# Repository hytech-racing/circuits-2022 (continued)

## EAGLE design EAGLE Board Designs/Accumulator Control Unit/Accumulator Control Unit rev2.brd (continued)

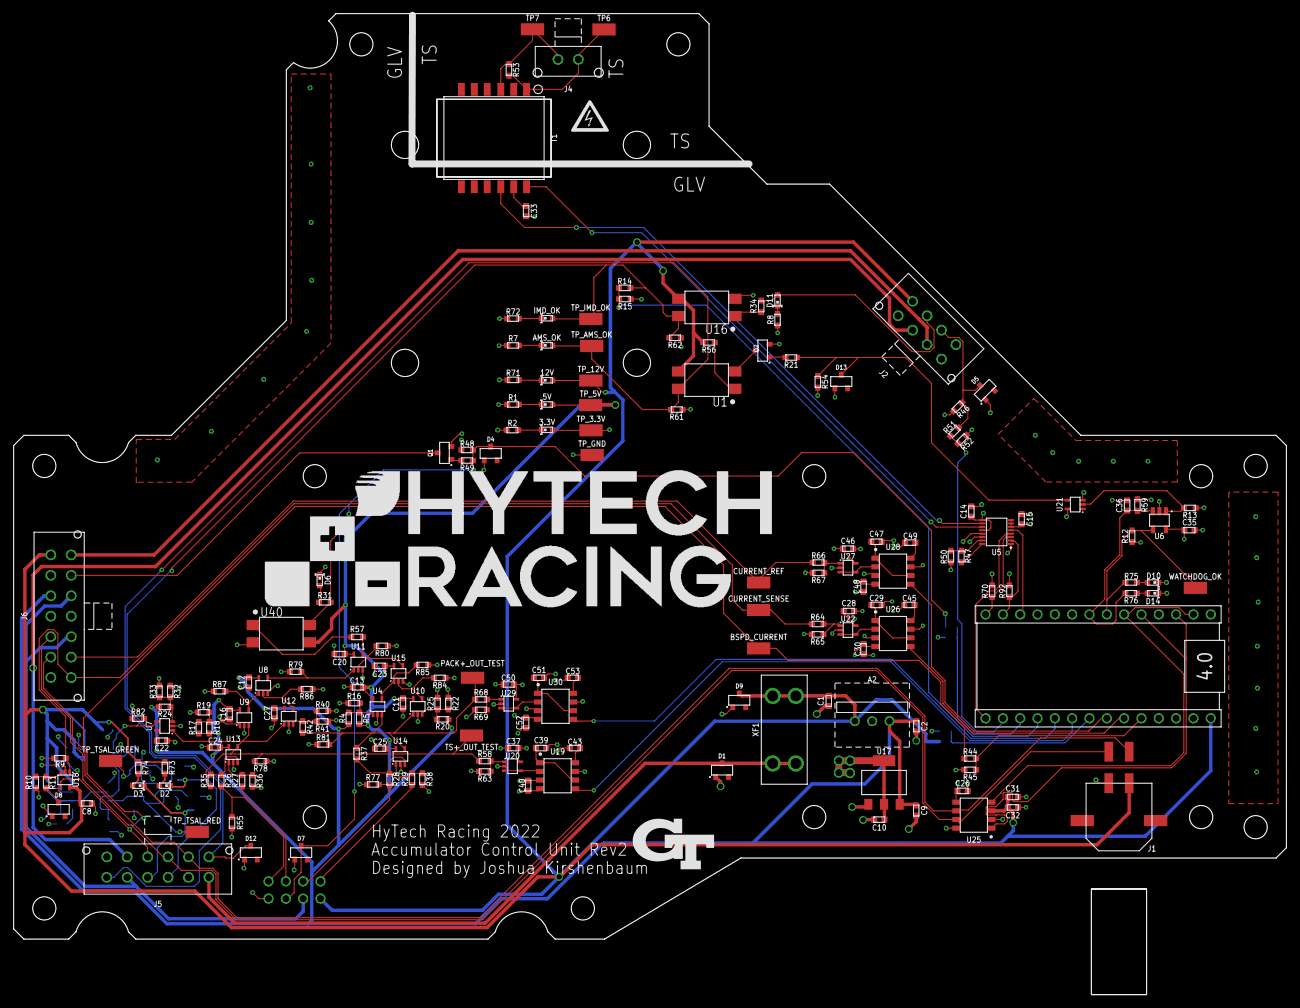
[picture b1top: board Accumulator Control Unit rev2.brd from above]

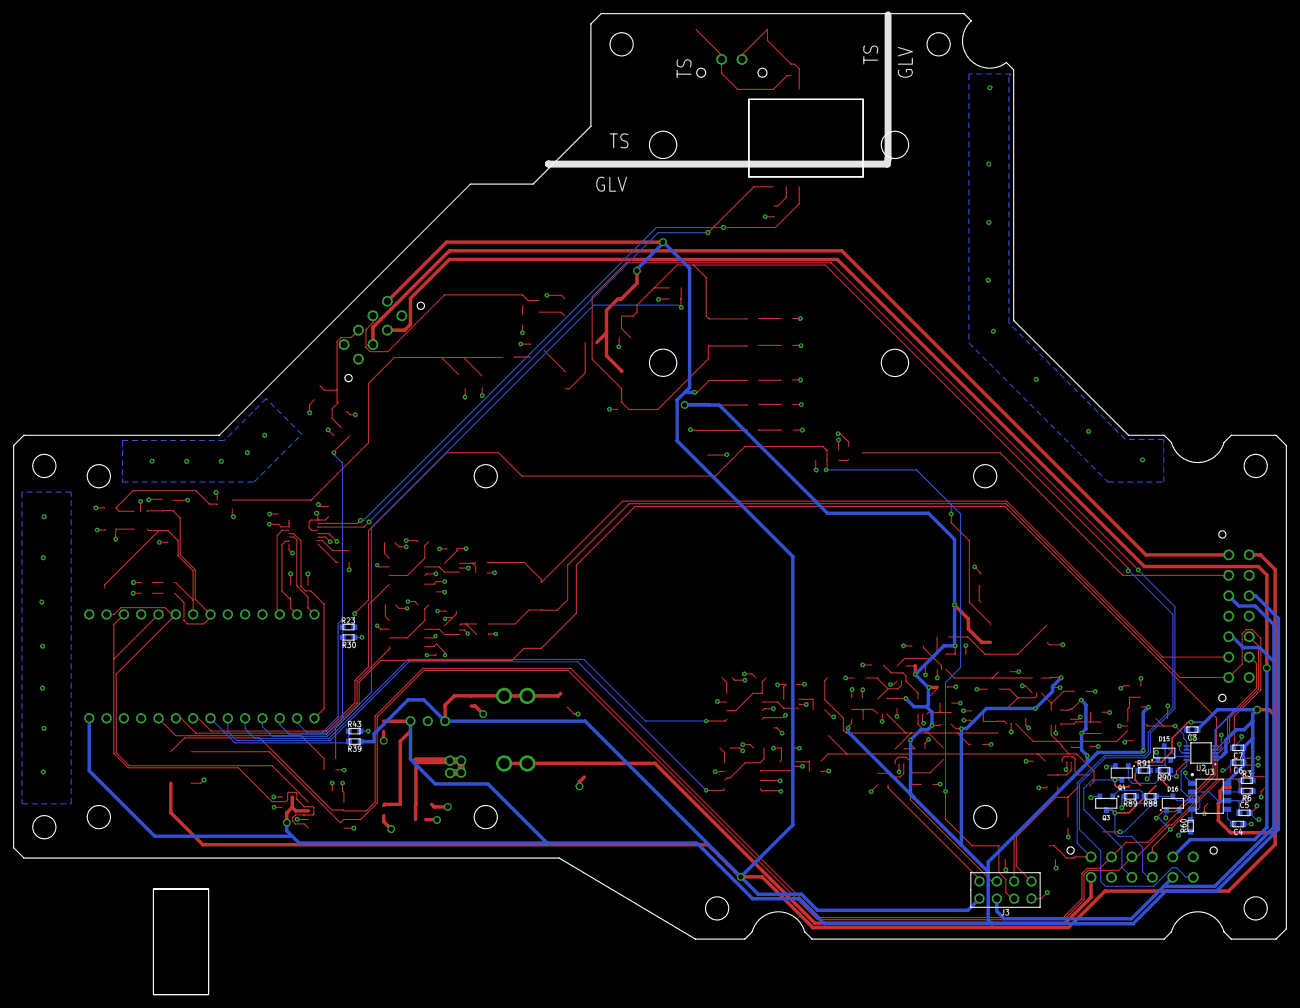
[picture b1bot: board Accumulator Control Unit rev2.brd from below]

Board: 4 copper layers, 186.7 x 143.9 mm, 236 parts (23 on the bottom side), 112 nets.

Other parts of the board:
U$1, U$5: GLV
U$3, U$9, U$10: TS
U$4: HV_0.50"
U$6, U$7, U$8, U$11, U$12, U$13, U$14, U$17, U$18, U$19, U$20, U$21, U$22: MOUNTING_M3
U$15: LOGO_HYTECH_EXTRA_LARGE
U$16: LOGO_GT_0.50"

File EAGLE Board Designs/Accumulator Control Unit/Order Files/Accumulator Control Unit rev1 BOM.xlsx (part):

Qty | Value | Device | Package | Parts | Description | CAPACITANCE | COLOR | CURRENT | DKPN | MANUFACTURER | MOPN | MPN | POWER | RESET_VOLTAGE | RESISTANCE | TOLERANCE | VOLTAGE | VOLTAGE_CONTINUOUS | VOLTAGE_MAX | Column1
1 | ADG1423 | ADG1423 | MSOP-10 | U2 | ADG1423 Form-A/Form-C Analog Switch |  |  |  | ADG1423BRMZ-REEL7CT-ND | Analog Devices Inc. | 584-ADG1423BRMZ | ADG1423BRMZ
1 | ADM823 | ADM823 | SC-70-5 | U6 | ADM823 Watchdog |  |  |  | 505-ADM823TYKSZ-R7CT-ND | Analog Devices Inc. | 584-ADM823TYKSZ-R7 | ADM823TYKSZ-R7 |  | 3.08
24 | CAPACITOR_0603_10V_0.1UF | CAPACITOR_0603_10V_0.1UF | 0603-CAP | C11, C12, C13, C14, C15, C16, C20, C22, C23, C24, C25, C26, C27, C29, C30, C31,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 | Capacitor, Non-Polarized | 0.1µF |  |  | 720-1688-1-ND | Vishay Vitramon | 77-VJ0603Y104JXQPBC | VJ0603Y104JXQPW1BC |  |  |  | 0.05 | 10V
2 | CAPACITOR_0603_10V_10NF | CAPACITOR_0603_10V_10NF | 0603-CAP | C4, C33 | Capacitor, Non-Polarized | 10nF |  |  | 311-4054-1-ND | Yageo | 603-CC603KRX7R6BB103 | CC0603KRX7R6BB103 |  |  |  | 0.1 | 10V
1 | CAPACITOR_0603_10V_15PF | CAPACITOR_0603_10V_15PF | 0603-CAP | C34 | Capacitor, Non-Polarized | 15pF |  |  | 720-VJ0603A150FXQPW1BCCT-ND | Vishay Vitramon | 77-VJ0603A150FXQPBC | VJ0603A150FXQPW1BC |  |  |  | 0.01 | 10V
2 | CAPACITOR_0603_10V_1UF | CAPACITOR_0603_10V_1UF | 0603-CAP | C9, C32 | Capacitor, Non-Polarized | 1µF |  |  | 311-1796-1-ND | Yageo | 603-CC603KRX7R6BB105 | CC0603KRX7R6BB105 |  |  |  | 0.1 | 10V
2 | CAPACITOR_0603_10V_4.7UF | CAPACITOR_0603_10V_4.7UF | 0603-CAP | C5, C10 | Capacitor, Non-Polarized | 4.7µF |  |  | 1276-1044-1-ND | Samsung Electro-Mechanics | 187-CL10A475KP8NNNC | CL10A475KP8NNNC |  |  |  | 0.1 | 10V
4 | CAPACITOR_0603_10V_680PF | CAPACITOR_0603_10V_680PF | 0603-CAP | C43, C45, C49, C53 | Capacitor, Non-Polarized | 680pF |  |  | 732-7757-1-ND | Würth Elektronik | 710-885012006013 | 885012006013 |  |  |  | 0.05 | 10V
6 | CAPACITOR_0603_25V_0.1UF | CAPACITOR_0603_25V_0.1UF | 0603-CAP | C7, C8, C28, C37, C46, C50 | Capacitor, Non-Polarized | 0.1µF |  |  | 1276-1006-1-ND | Samsung Electro-Mechanics | 187-CL10B104KA8NNNC | CL10B104KA8NNNC |  |  |  | 0.1 | 25V
2 | CAPACITOR_0603_25V_10UF | CAPACITOR_0603_25V_10UF | 0603-CAP | C1, C2 | Capacitor, Non-Polarized | 10µF |  |  | 490-7202-1-ND | Murata Electronics | 81-GRM188R61E106MA3D | GRM188R61E106MA73D |  |  |  | 0.2 | 25V
2 | CAPACITOR_0603_25V_1UF | CAPACITOR_0603_25V_1UF | 0603-CAP | C3, C6 | Capacitor, Non-Polarized | 1µF |  |  | 1276-1184-1-ND | Samsung Electro-Mechanics | 187-CL10B105KA8NNNC | CL10B105KA8NNNC |  |  |  | 0.1 | 25V
1 | CONNECTOR-12_MF_T_V_ | CONNECTOR-12_MF_T_V_ | MOLEX_MICROFIT_PTH_VERTICAL_12_DUAL | J5 | 12 pin connector |  |  |  |  | MOLEX |  | 430451214
1 | CONNECTOR-14_MF_T_V_ | CONNECTOR-14_MF_T_V_ | MOLEX_MICROFIT_PTH_VERTICAL_14_DUAL | J6 | 14 pin connector |  |  |  |  | MOLEX |  | 430451414
1 | CONNECTOR-2_MF_T_V_ | CONNECTOR-2_MF_T_V_ | MOLEX_MICROFIT_PTH_VERTICAL_02_SINGLE | J4 | 2 Pin Connector |  |  |  |  | MOLEX |  | 436500217
2 | CONNECTOR-8_MF_T_V_ | CONNECTOR-8_MF_T_V_ | MOLEX_MICROFIT_PTH_VERTICAL_08_DUAL | J2, J3 | 8 Pin Connector |  |  |  |  | MOLEX |  | 430450814
1 | CONNECTOR-CAN_MF_T_V_ | CONNECTOR-CAN_MF_T_V_ | MOLEX_MICROFIT_PTH_VERTICAL_04_DUAL | J1 | HyTech CAN Connector |  |  |  |  | Molex |  | 430450414
1 | FUSE_MINI-BLADE_1A | FUSE_MINI-BLADE_1A | MINI-BLADE_FUSE_HOLDER | F1 | Fuse |  |  | 1A
1 | LED_0603_BLUE | LED_0603_BLUE | 0603-LED | 5V | LED |  | Blue |  | 754-1789-1-ND | Kingbright | 604-APT1608VBC/D | APT1608VBC/D
4 | LED_0603_GREEN | LED_0603_GREEN | 0603-LED | 3.3V, AMS_OK, D2, D10 | LED |  | Green |  | 754-1790-1-ND | Kingbright | 604-APT1608ZGCK | APT1608ZGCK
1 | LED_0603_ORANGE | LED_0603_ORANGE | 0603-LED | IMD_OK | LED |  | Orange |  | 754-1120-1-ND | Kingbright | 604-APT1608SECK | APT1608SECK
4 | LED_0603_RED | LED_0603_RED | 0603-LED | 12V, D3, D6, D14 | LED |  | Red |  | 754-1786-1-ND | Kingbright | 604-APT1608SECKJ3PRV | APT1608SECK/J3-PRV
1 | LED_0603_YELLOW | LED_0603_YELLOW | 0603-LED | D11 | LED |  | Yellow |  | 754-1788-1-ND | Kingbright | 604-APT1608SYCK/J3-PRV | APT1608SYCK/J3-PRV
1 | LM555 | LM555 | SOIC-08(NARROW,0.15)" | U3 | **555 Precision Timer |  |  |  | LM555CMX/NOPBCT-ND | Texas Instruments | 926-LM555CMX/NOPB | LM555CMX/NOPB
3 | LOGICGATE_AND_DCK3 | LOGICGATE_AND_DCK3 | SC-70-5 | U8, U11, U15 | AND Gate |  |  |  | 296-SN74LVC1G08DCK3TR-ND | Texas Instruments | 595-SN74LVC1G08DCK3 | SN74LVC1G08DCK3
1 | LTC6820 | LTC6820 | MSOP-16 | U5 | LTC6820 isoSPI Isolated Communications Interface |  |  |  |  | Analog Devices |  | LTC6820IMS#PBF
4 | MAX7404 | MAX7404 | SOIC-08(NARROW,0.15)" | U19, U26, U28, U30 | 8th-Order Maxim Filter |  |  |  | MAX7404CSA+-ND | Maxim Integrated | 700-MAX7404CSA | MAX7404CSA+
12 | OPAMP_1_CHANNEL_OPA991 | OPAMP_1_CHANNEL_OPA991 | SC-70-5 | U4, U7, U9, U10, U12, U13, U14, U18, U20, U22, U27, U29 | Op-Amp 1 Channel |  |  |  | 296-OPA991IDCKRCT-ND | Texas Instruments | 595-OPA991IDCKR | OPA991IDCKR
3 | RELAY_SOLIDSTATE_NO | RELAY_SOLIDSTATE_NO | DIP-4 | U$2, U1, U16 | AQY214EH Normally Open Solid State Relay |  |  |  |  |  |  | AQY214EHA
1 | RESISTOR_0603_1.4K | RESISTOR_0603_1.4K | 0603-RES | R11 | Resistor |  |  |  | 311-2465-1-ND | Yageo | 603-RT0603DRE071K4L | RT0603DRE071K4L | 0.1W |  | 1.4K | 5.0000000000000001E-3 |  | 75V | 75V
2 | RESISTOR_0603_10 | RESISTOR_0603_10 | 0603-RES | R21, R49 | Resistor |  |  |  | 311-10.0HRCT-ND | Yageo | 603-RC0603FR-0710RL | RC0603FR-0710RL | 0.1W |  | 10 | 0.01 |  | 1V | 75V
2 | RESISTOR_0603_10.2K | RESISTOR_0603_10.2K | 0603-RES | R16, R19 | Resistor |  |  |  | P10.2KDBCT-ND | Panasonic Electronic Components | 667-ERA-3AEB1022V | ERA-3AEB1022V | 0.1W |  | 10.2k | 1E-3 |  | 31.94V | 75V
4 | RESISTOR_0603_10.5K | RESISTOR_0603_10.5K | 0603-RES | R35, R36, R37, R38 | Resistor |  |  |  | P10.5KDBCT-ND | Panasonic Electronic Components | 677-ERA-3AEB1052V | ERA-3AEB1052V | 0.1W |  | 10.5k | 1E-3 |  | 32.40V | 75V
1 | RESISTOR_0603_100K | RESISTOR_0603_100K | 0603-RES | R13 | Resistor |  |  |  | YAG2294CT-ND | Yageo | 603-RC0603JR-10100KL | RC0603JR-10100KL | 0.1W |  | 100k | 0.05 |  | 75V | 75V
23 | RESISTOR_0603_10K | RESISTOR_0603_10K | 0603-RES | R9, R12, R23, R48, R54, R55, R58, R60, R61, R62, R64, R66, R68, R77, R78, R79, 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 | Resistor |  |  |  | 311-10.0KHRCT-ND | Yageo | 603-RC0603FR-0710KL | RC0603FR-0710KL | 0.1W |  | 10k | 0.01 |  | 31.62V | 75V
1 | RESISTOR_0603_11.3K | RESISTOR_0603_11.3K | 0603-RES | R42 | Resistor |  |  |  | P11.3KDBCT-ND | Panasonic Electronic Components | 667-ERA-3AEB1132V | ERA-3AEB1132V | 0.1W |  | 11.3k | 1E-3 |  | 33.62V | 75V
7 | RESISTOR_0603_11.5K | RESISTOR_0603_11.5K | 0603-RES | R20, R25, R26, R27, R28, R29, R33 | Resistor |  |  |  | P11.5KDBCT-ND | Panasonic Electronic Components | 667-ERA-3AEB1152V | ERA-3AEB1152V | 0.1W |  | 11.5k | 1E-3 |  | 33.91V | 75V
9 | RESISTOR_0603_12K | RESISTOR_0603_12K | 0603-RES | R15, R30, R43, R45, R52, R63, R65, R67, R69 | Resistor |  |  |  | 311-12.0KHRCT-ND | Yageo | 603-RC0603FR-0712KL | RC0603FR-0712KL | 0.1W |  | 12k | 0.01 |  | 34.64V | 75V
12 | RESISTOR_0603_1K | RESISTOR_0603_1K | 0603-RES | R1, R2, R3, R7, R8, R10, R31, R47, R50, R59, R70, R71 | Resistor |  |  |  | 311-1.00KHRCT-ND | Yageo | 603-RC0603FR-071KL | RC0603FR-071KL | 0.1W |  | 1k | 0.01 |  | 10.00V | 75V
1 | RESISTOR_0603_2.2K | RESISTOR_0603_2.2K | 0603-RES | R46 | Resistor |  |  |  | 13-RC0603DR-072K2LCT-ND | Yageo | 603-RC0603DR-072K2L | RC0603DR-072K2L | 0.1W |  | 2.2k | 5.0000000000000001E-3 |  | 75V | 75V
1 | RESISTOR_0603_215K | RESISTOR_0603_215K | 0603-RES | R41 | Resistor |  |  |  | P215KDBCT-ND | Panasonic Electronic Components | 667-ERA-3AEB2153V | ERA-3AEB2153V | 0.1W |  | 215k | 1E-3 |  | 75V | 75V
5 | RESISTOR_0603_2K | RESISTOR_0603_2K | 0603-RES | R34, R56, R72, R73, R74 | Resistor |  |  |  | P2.0KBDCT-ND | Panasonic Electronic Components | 667-ERA-3ARB202V | ERA-3ARB202V | 0.1W |  | 2k | 1E-3 |  | 14.14V | 75V
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
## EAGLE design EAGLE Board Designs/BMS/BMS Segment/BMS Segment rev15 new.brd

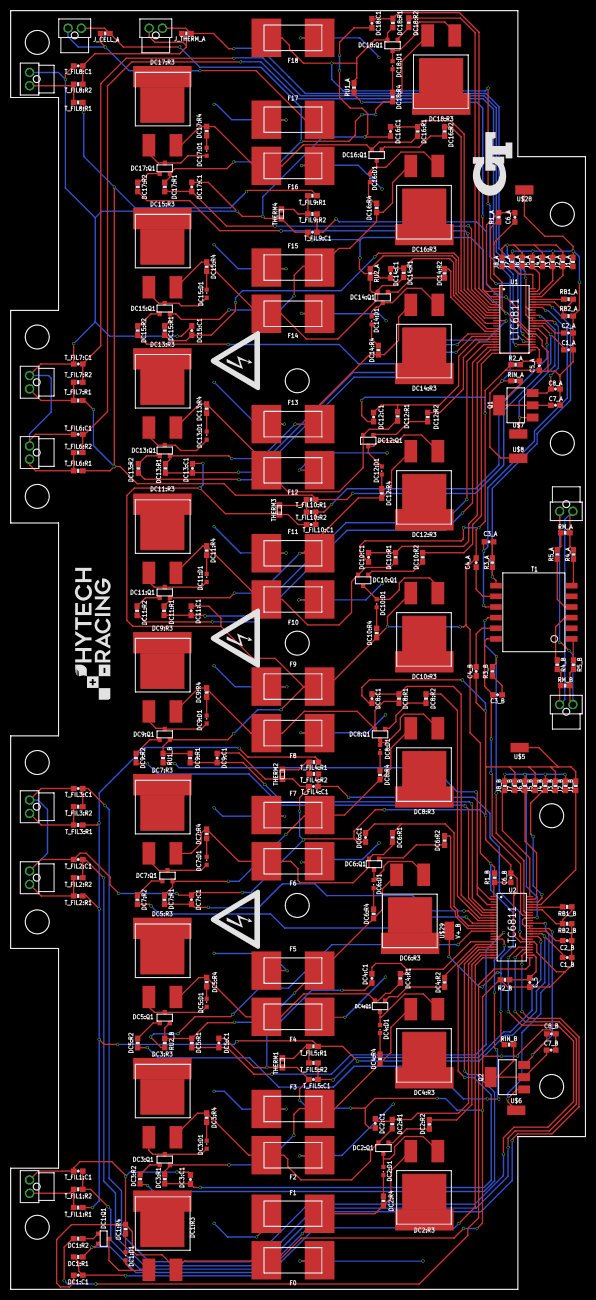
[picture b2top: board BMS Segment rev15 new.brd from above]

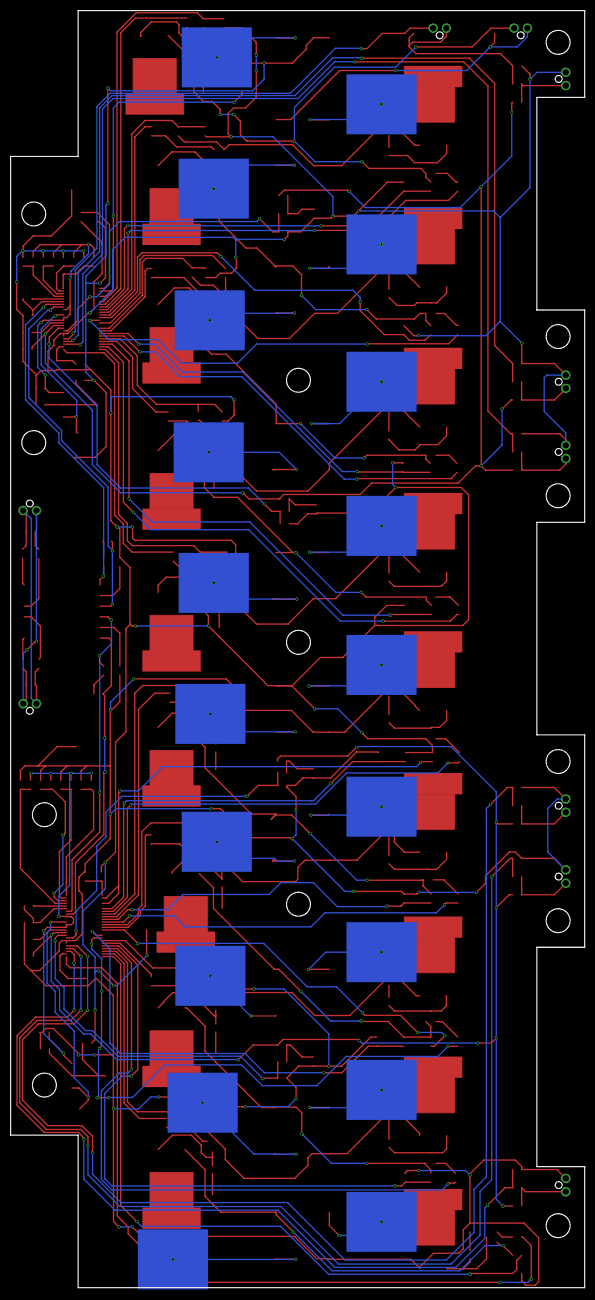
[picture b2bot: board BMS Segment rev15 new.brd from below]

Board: 2 copper layers, 108.0 x 240.3 mm, 294 parts (19 on the bottom side), 194 nets.

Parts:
AMS_CELL_TEST: AMS_CELL_TEST; NANO-FIT_VERTICAL-2
AMS_THERM_TEST: AMS_THERM_TEST; NANO-FIT_VERTICAL-2
C1_A, C1_B, C2_A, C2_B, C8_A, C8_B: 1uF; 0603-CAP
C3_A, C3_B: 15pF; 0603-CAP
C4_A, C4_B, C5_A: 10nF; 0603-CAP
C6_A, C6_B, C7_A, C7_B: 100nF; 0603-CAP
CELL0, CELL1, CELL2, CELL3, CELL4, CELL5, CELL6, CELL7, CELL8, CELL9, CELL10, CELL11, CELL12, CELL13, CELL14, CELL15, CELL16, CELL17, CELL18: BATTERY_SPRING_KEYSTONE5222; KEYSTONE5222
C_5: 10nF; 0603-CAP
DC1:C1, DC2:C1, DC3:C1, DC4:C1, DC5:C1, DC6:C1, DC7:C1, DC8:C1, DC9:C1, DC10:C1, DC11:C1, DC12:C1, DC13:C1, DC14:C1, DC15:C1, DC16:C1, DC17:C1, DC18:C1: 10nF; 0603-CAP
DC1:D1, DC2:D1, DC3:D1, DC4:D1, DC5:D1, DC6:D1, DC7:D1, DC8:D1, DC9:D1, DC10:D1, DC11:D1, DC12:D1, DC13:D1, DC14:D1, DC15:D1, DC16:D1, DC17:D1, DC18:D1: RED; LED-603
DC1:Q1, DC2:Q1, DC3:Q1, DC4:Q1, DC5:Q1, DC6:Q1, DC7:Q1, DC8:Q1, DC9:Q1, DC10:Q1, DC11:Q1, DC12:Q1, DC13:Q1, DC14:Q1, DC15:Q1, DC16:Q1, DC17:Q1, DC18:Q1: P-CHANNEL_MOSFET_DMP3099L-7; SOT23
DC1:R1, DC2:R1, DC3:R1, DC4:R1, DC5:R1, DC6:R1, DC7:R1, DC8:R1, DC9:R1, DC10:R1, DC11:R1, DC12:R1, DC13:R1, DC14:R1, DC15:R1, DC16:R1, DC17:R1, DC18:R1: 100R; 0603-RES@1
DC1:R2, DC2:R2, DC3:R2, DC4:R2, DC5:R2, DC6:R2, DC7:R2, DC8:R2, DC9:R2, DC10:R2, DC11:R2, DC12:R2, DC13:R2, DC14:R2, DC15:R2, DC16:R2, DC17:R2, DC18:R2: 3K3; 0603-RES@1
DC1:R3, DC2:R3, DC3:R3, DC4:R3, DC5:R3, DC6:R3, DC7:R3, DC8:R3, DC9:R3, DC10:R3, DC11:R3, DC12:R3, DC13:R3, DC14:R3, DC15:R3, DC16:R3, DC17:R3, DC18:R3: RESISTOR_PWR263_; PWR263
DC1:R4, DC2:R4, DC3:R4, DC4:R4, DC5:R4, DC6:R4, DC7:R4, DC8:R4, DC9:R4, DC10:R4, DC11:R4, DC12:R4, DC13:R4, DC14:R4, DC15:R4, DC16:R4, DC17:R4, DC18:R4: 806R; 0603-RES@1
F0, F1, F2, F3, F4, F5, F6, F7, F8, F9, F10, F11, F12, F13, F14, F15, F16, F17, F18: 0001.2704.11; 0885
ISOSPI_A: ISOSPI; NANO-FIT_VERTICAL-2
ISOSPI_B: ISOSPI; NANO-FIT_VERTICAL-2
J1_A, J1_B, J2_A, J2_B, J3_A, J3_B, J4_A, J4_B, J5_A, J5_B, J6_A, J6_B, J7_A, J7_B, J8_A, J8_B: 0R; 0603-RES@1
J_CELL_A: 0R; 0603-RES@1
J_THERM_A: 0R; 0603-RES@1
Q1, Q2: NSV1C201MZ4; SOT223
R1_A, R1_B, R2_A, R2_B: 100R; 0603-RES@1
R3_A, R3_B: 402R; 0603-RES@1
R4_A, R4_B, R5_A, R5_B: 22R; 0603-RES@1
RB1_A, RB1_B: 1K2; 0603-RES@1
RB2_A, RB2_B: 806R; 0603-RES@1
RIN_A: 100R; 0603-RES@1
RIN_B: 100R; 0603-RES@1
RM_A: 100R; 0603-RES@1
RM_B: 100R; 0603-RES@1
RU1_A, RU1_B, RU2_A, RU2_B: 100R; 0603-RES@1
T1: HM2102NLT
THERM1, THERM2, THERM3, THERM4: 10K; 0603
THERM1_A, THERM1_B, THERM2_A, THERM2_B, THERM3_A, THERM3_B: THERMISTOR; NANO-FIT_VERTICAL-2
T_FIL1:C1, T_FIL2:C1, T_FIL3:C1, T_FIL4:C1, T_FIL5:C1, T_FIL6:C1, T_FIL7:C1, T_FIL8:C1, T_FIL9:C1, T_FIL10:C1: 10nF; 0603-CAP
T_FIL1:R1, T_FIL2:R1, T_FIL3:R1, T_FIL4:R1, T_FIL5:R1, T_FIL6:R1, T_FIL7:R1, T_FIL8:R1, T_FIL9:R1, T_FIL10:R1: 10K; 0603-RES@1
T_FIL1:R2, T_FIL2:R2, T_FIL3:R2, T_FIL4:R2, T_FIL5:R2, T_FIL6:R2, T_FIL7:R2, T_FIL8:R2, T_FIL9:R2, T_FIL10:R2: 100R; 0603-RES@1
U1, U2: LTC6811-2; LTC6811
U$1: LOGO_HYTECH_1.0"
U$2: LOGO_GT_0.50"
U$3, U$4, U$20: HV_1.00"
U$5, U$6, U$7, U$8, U$28, U$29: TEST_POINTMICRO_MINIATURE; MICRO_MINIATURE
U$9, U$10, U$11, U$12, U$13, U$14, U$15, U$16, U$17, U$18, U$19, U$26, U$27: M4_MOUNTING
U$21: NUMBER

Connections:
C0_A: C5_A.1, R2_A.2, U1.26
C0_B: C_5.1, R2_B.2, U2.26
C1_A: DC10:C1.1, DC10:R1.2, U1.24
C1_B: DC1:C1.1, DC1:R1.2, U2.24
C2_A: DC11:C1.1, DC11:R1.2, U1.22
C2_B: DC2:C1.1, DC2:R1.2, U2.22
C3_A: DC12:C1.1, DC12:R1.2, U1.20
C3_B: DC3:C1.1, DC3:R1.2, U2.20
C4_A: DC13:C1.1, DC13:R1.2, U1.18
C4_B: DC4:C1.1, DC4:R1.2, U2.18
C5_A: DC14:C1.1, DC14:R1.2, U1.16
C5_B: DC5:C1.1, DC5:R1.2, U2.16
C7_A: DC15:C1.1, DC15:R1.2, U1.12
C7_B: DC6:C1.1, DC6:R1.2, U2.12
C8_A: DC16:C1.1, DC16:R1.2, U1.10
C8_B: DC7:C1.1, DC7:R1.2, U2.10
C9_A: DC17:C1.1, DC17:R1.2, U1.8
C9_B: DC8:C1.1, DC8:R1.2, U2.8
C10_A: DC18:C1.1, DC18:R1.2, U1.6
C10_B: DC9:C1.1, DC9:R1.2, U2.6
CC0: CELL0.1, F0.1
CC1: CELL1.1, F1.1
CC2: CELL2.1, F2.1
CC3: CELL3.1, F3.1
CC4: CELL4.1, F4.1
CC5: CELL5.1, F5.1
CC6: CELL6.1, F6.1
CC7: CELL7.1, F7.1
CC8: CELL8.1, F8.1
CC9: CELL9.1, F9.1
CC10: CELL10.1, F10.1
CC11: CELL11.1, F11.1
CC12: CELL12.1, F12.1
CC13: CELL13.1, F13.1
CC14: CELL14.1, F14.1
CC15: CELL15.1, F15.1
CC16: CELL16.1, F16.1
CC17: CELL17.1, F17.1
CC18: CELL18.1, F18.1
DC1:GATE: DC1:Q1.1, DC1:R2.1
DC1:N$1: DC1:D1.A, DC1:Q1.3, DC1:R3.1
DC1:N$2: DC1:D1.C, DC1:R4.2
DC2:GATE: DC2:Q1.1, DC2:R2.1
DC2:N$1: DC2:D1.A, DC2:Q1.3, DC2:R3.1
DC2:N$2: DC2:D1.C, DC2:R4.2
DC3:GATE: DC3:Q1.1, DC3:R2.1
DC3:N$1: DC3:D1.A, DC3:Q1.3, DC3:R3.1
DC3:N$2: DC3:D1.C, DC3:R4.2
DC4:GATE: DC4:Q1.1, DC4:R2.1
DC4:N$1: DC4:D1.A, DC4:Q1.3, DC4:R3.1
DC4:N$2: DC4:D1.C, DC4:R4.2
DC5:GATE: DC5:Q1.1, DC5:R2.1
DC5:N$1: DC5:D1.A, DC5:Q1.3, DC5:R3.1
DC5:N$2: DC5:D1.C, DC5:R4.2
DC6:GATE: DC6:Q1.1, DC6:R2.1
DC6:N$1: DC6:D1.A, DC6:Q1.3, DC6:R3.1
DC6:N$2: DC6:D1.C, DC6:R4.2
DC7:GATE: DC7:Q1.1, DC7:R2.1
DC7:N$1: DC7:D1.A, DC7:Q1.3, DC7:R3.1
DC7:N$2: DC7:D1.C, DC7:R4.2
DC8:GATE: DC8:Q1.1, DC8:R2.1
DC8:N$1: DC8:D1.A, DC8:Q1.3, DC8:R3.1
DC8:N$2: DC8:D1.C, DC8:R4.2
DC9:GATE: DC9:Q1.1, DC9:R2.1
DC9:N$1: DC9:D1.A, DC9:Q1.3, DC9:R3.1
DC9:N$2: DC9:D1.C, DC9:R4.2
DC10:GATE: DC10:Q1.1, DC10:R2.1
DC10:N$1: DC10:D1.A, DC10:Q1.3, DC10:R3.1
DC10:N$2: DC10:D1.C, DC10:R4.2
DC11:GATE: DC11:Q1.1, DC11:R2.1
DC11:N$1: DC11:D1.A, DC11:Q1.3, DC11:R3.1
DC11:N$2: DC11:D1.C, DC11:R4.2
DC12:GATE: DC12:Q1.1, DC12:R2.1
DC12:N$1: DC12:D1.A, DC12:Q1.3, DC12:R3.1
DC12:N$2: DC12:D1.C, DC12:R4.2
DC13:GATE: DC13:Q1.1, DC13:R2.1
DC13:N$1: DC13:D1.A, DC13:Q1.3, DC13:R3.1
DC13:N$2: DC13:D1.C, DC13:R4.2
DC14:GATE: DC14:Q1.1, DC14:R2.1
DC14:N$1: DC14:D1.A, DC14:Q1.3, DC14:R3.1
DC14:N$2: DC14:D1.C, DC14:R4.2
DC15:GATE: DC15:Q1.1, DC15:R2.1
DC15:N$1: DC15:D1.A, DC15:Q1.3, DC15:R3.1
DC15:N$2: DC15:D1.C, DC15:R4.2
DC16:GATE: DC16:Q1.1, DC16:R2.1
DC16:N$1: DC16:D1.A, DC16:Q1.3, DC16:R3.1
DC16:N$2: DC16:D1.C, DC16:R4.2
DC17:GATE: DC17:Q1.1, DC17:R2.1
DC17:N$1: DC17:D1.A, DC17:Q1.3, DC17:R3.1
DC17:N$2: DC17:D1.C, DC17:R4.2
DC18:GATE: DC18:Q1.1, DC18:R2.1
DC18:N$1: DC18:D1.A, DC18:Q1.3, DC18:R3.1
DC18:N$2: DC18:D1.C, DC18:R4.2
DRIVE_A: Q1.1, U1.38, U$7.1
DRIVE_B: Q2.1, U2.38, U$6.1
GPIO1_A: T_FIL6:C1.1, T_FIL6:R2.1, U1.27
GPIO1_B: T_FIL1:C1.1, T_FIL1:R2.1, U2.27
GPIO2_A: T_FIL7:C1.1, T_FIL7:R2.1, U1.28
GPIO2_B: T_FIL2:C1.1, T_FIL2:R2.1, U2.28
GPIO3_A_POST: AMS_THERM_TEST.P$2, J_THERM_A.1, U1.29
GPIO3_A_PRE: AMS_THERM_TEST.P$1, J_THERM_A.2, T_FIL8:C1.1, T_FIL8:R2.1
GPIO3_B: T_FIL3:C1.1, T_FIL3:R2.1, U2.29
GPIO4_A: T_FIL9:C1.1, T_FIL9:R2.1, U1.32
GPIO4_B: T_FIL4:C1.1, T_FIL4:R2.1, U2.32
GPIO5_A: T_FIL10:C1.1, T_FIL10:R2.1, U1.33
GPIO5_B: T_FIL5:C1.1, T_FIL5:R2.1, U2.33
IM_A: C3_A.2, T1.P$9, U1.41
IM_B: C3_B.2, T1.P$12, U2.41
IP_A: R3_A.1, T1.P$7, U1.42
IP_B: R3_B.1, T1.P$10, U2.42
ISOSPI-M: ISOSPI_A.P$2, ISOSPI_B.P$2, R5_A.2, R5_B.2, RM_A.2, RM_B.2
ISOSPI-P: ISOSPI_A.P$1, ISOSPI_B.P$1, R4_A.2, R4_B.2, RM_A.1, RM_B.1
unnamed: C4_B.1, T1.P$11
unnamed: RB1_B.2, U2.44
unnamed: THERM1_B.P$1, T_FIL1:R1.2, T_FIL1:R2.2
unnamed: RB1_B.1, RB2_B.2, U2.43
unnamed: R4_B.1, T1.P$3
unnamed: RB1_A.2, U1.44
unnamed: R5_B.1, T1.P$1
unnamed: J7_B.1, J8_B.1, U2.48
unnamed: J5_B.1, J6_B.1, U2.47
unnamed: C3_B.1, R3_B.2
unnamed: J3_B.1, J4_B.1, U2.46
unnamed: J1_B.1, J2_B.1, U2.45
unnamed: THERM1.2, T_FIL5:R1.2, T_FIL5:R2.2
unnamed: THERM2_B.P$1, T_FIL2:R1.2, T_FIL2:R2.2
unnamed: THERM2.2, T_FIL4:R1.2, T_FIL4:R2.2
unnamed: RB1_A.1, RB2_A.2, U1.43
unnamed: C4_A.1, T1.P$8
unnamed: R4_A.1, T1.P$6
unnamed: R5_A.1, T1.P$4
unnamed: C3_A.1, R3_A.2
unnamed: THERM3_B.P$1, T_FIL3:R1.2, T_FIL3:R2.2
unnamed: J7_A.1, J8_A.1, U1.48
unnamed: J5_A.1, J6_A.1, U1.47
unnamed: J3_A.1, J4_A.1, U1.46
unnamed: J1_A.1, J2_A.1, U1.45
unnamed: THERM4.2, T_FIL9:R1.2, T_FIL9:R2.2
unnamed: THERM3_A.P$1, T_FIL8:R1.2, T_FIL8:R2.2
unnamed: THERM3.2, T_FIL10:R1.2, T_FIL10:R2.2
unnamed: THERM2_A.P$1, T_FIL7:R1.2, T_FIL7:R2.2
unnamed: THERM1_A.P$1, T_FIL6:R1.2, T_FIL6:R2.2
S1_A: DC10:R2.2, U1.25
S1_B: DC1:R2.2, U2.25
S2_A: DC11:R2.2, U1.23
S2_B: DC2:R2.2, U2.23
S3_A: DC12:R2.2, U1.21
S3_B: DC3:R2.2, U2.21
S4_A: DC13:R2.2, U1.19
S4_B: DC4:R2.2, U2.19
S5_A: DC14:R2.2, U1.17
S5_B: DC5:R2.2, U2.17
S7_A: DC15:R2.2, U1.13
S7_B: DC6:R2.2, U2.13
S8_A: DC16:R2.2, U1.11
S8_B: DC7:R2.2, U2.11
S9_A: DC17:R2.2, U1.9
S9_B: DC8:R2.2, U2.9
S10_A: DC18:R2.2, U1.7
S10_B: DC9:R2.2, U2.7
SENSE1: DC1:Q1.2, DC1:R1.1, DC2:R3.2, DC2:R4.1, F1.2
SENSE2: DC2:Q1.2, DC2:R1.1, DC3:R3.2, DC3:R4.1, F2.2
SENSE3: DC3:Q1.2, DC3:R1.1, DC4:R3.2, DC4:R4.1, F3.2
SENSE4: DC4:Q1.2, DC4:R1.1, DC5:R3.2, DC5:R4.1, F4.2
SENSE5: DC5:Q1.2, DC5:R1.1, DC6:R3.2, DC6:R4.1, F5.2, RU2_B.1
SENSE6: DC6:Q1.2, DC6:R1.1, DC7:R3.2, DC7:R4.1, F6.2
SENSE7: DC7:Q1.2, DC7:R1.1, DC8:R3.2, DC8:R4.1, F7.2
SENSE8: DC8:Q1.2, DC8:R1.1, DC9:R3.2, DC9:R4.1, F8.2
SENSE10: DC10:Q1.2, DC10:R1.1, DC11:R3.2, DC11:R4.1, F10.2
SENSE11: DC11:Q1.2, DC11:R1.1, DC12:R3.2, DC12:R4.1, F11.2
SENSE12: DC12:Q1.2, DC12:R1.1, DC13:R3.2, DC13:R4.1, F12.2
SENSE13: DC13:Q1.2, DC13:R1.1, DC14:R3.2, DC14:R4.1, F13.2
SENSE14: DC14:Q1.2, DC14:R1.1, DC15:R3.2, DC15:R4.1, F14.2, RU2_A.1
SENSE15: DC15:Q1.2, DC15:R1.1, DC16:R3.2, DC16:R4.1, F15.2
SENSE16: DC16:Q1.2, DC16:R1.1, DC17:R3.2, DC17:R4.1, F16.2
SENSE17_POST: AMS_CELL_TEST.P$2, DC17:Q1.2, DC17:R1.1, DC18:R3.2, DC18:R4.1, J_CELL_A.2
SENSE17_PRE: AMS_CELL_TEST.P$1, F17.2, J_CELL_A.1
SENSE18: DC18:Q1.2, DC18:R1.1, F18.2, R1_A.1, RIN_A.1, RU1_A.1, U$8.1
UNUSED1_A: RU1_A.2, U1.2, U1.4
UNUSED1_B: RU1_B.2, U2.2, U2.4
UNUSED2_A: RU2_A.2, U1.14
UNUSED2_B: RU2_B.2, U2.14
V+_A: C6_A.1, R1_A.2, U1.1
V+_B: C6_B.1, R1_B.2, U2.1
V-_A: C1_A.2, C2_A.2, C4_A.2, C5_A.2, C6_A.2, C7_A.2, C8_A.2, DC9:Q1.2, DC9:R1.1, DC10:C1.2, DC10:R3.2, DC10:R4.1, DC11:C1.2, DC12:C1.2, DC13:C1.2, DC14:C1.2, DC15:C1.2, DC16:C1.2, DC17:C1.2, DC18:C1.2, F9.2, J1_A.2, J3_A.2, J5_A.2, J7_A.2, R1_B.1, R2_A.1, RB2_A.1, RIN_B.1, RU1_B.1, THERM1_A.P$2, THERM2_A.P$2, THERM3.1, THERM3_A.P$2, THERM4.1, T_FIL6:C1.2, T_FIL7:C1.2, T_FIL8:C1.2, T_FIL9:C1.2, T_FIL10:C1.2, U1.30, U1.31, U$28.1, U$29.1
V-_B: C1_B.2, C2_B.2, C4_B.2, C6_B.2, C7_B.2, C8_B.2, C_5.2, DC1:C1.2, DC1:R3.2, DC1:R4.1, DC2:C1.2, DC3:C1.2, DC4:C1.2, DC5:C1.2, DC6:C1.2, DC7:C1.2, DC8:C1.2, DC9:C1.2, F0.2, J1_B.2, J3_B.2, J5_B.2, J7_B.2, R2_B.1, RB2_B.1, THERM1.1, THERM1_B.P$2, THERM2.1, THERM2_B.P$2, THERM3_B.P$2, T_FIL1:C1.2, T_FIL2:C1.2, T_FIL3:C1.2, T_FIL4:C1.2, T_FIL5:C1.2, U2.30, U2.31, U$5.1
VIN_A: C7_A.1, Q1.2, Q1.4, RIN_A.2
VIN_B: C7_B.1, Q2.2, Q2.4, RIN_B.2
VREF1_A: C2_A.1, U1.35
VREF1_B: C2_B.1, U2.35
VREF2_A: C1_A.1, T_FIL6:R1.1, T_FIL7:R1.1, T_FIL8:R1.1, T_FIL9:R1.1, T_FIL10:R1.1, U1.34
VREF2_B: C1_B.1, T_FIL1:R1.1, T_FIL2:R1.1, T_FIL3:R1.1, T_FIL4:R1.1, T_FIL5:R1.1, U2.34
VREG_A: C8_A.1, J2_A.2, J4_A.2, J6_A.2, J8_A.2, Q1.3, U1.36, U1.37, U1.40
VREG_B: C8_B.1, J2_B.2, J4_B.2, J6_B.2, J8_B.2, Q2.3, U2.36, U2.37, U2.40

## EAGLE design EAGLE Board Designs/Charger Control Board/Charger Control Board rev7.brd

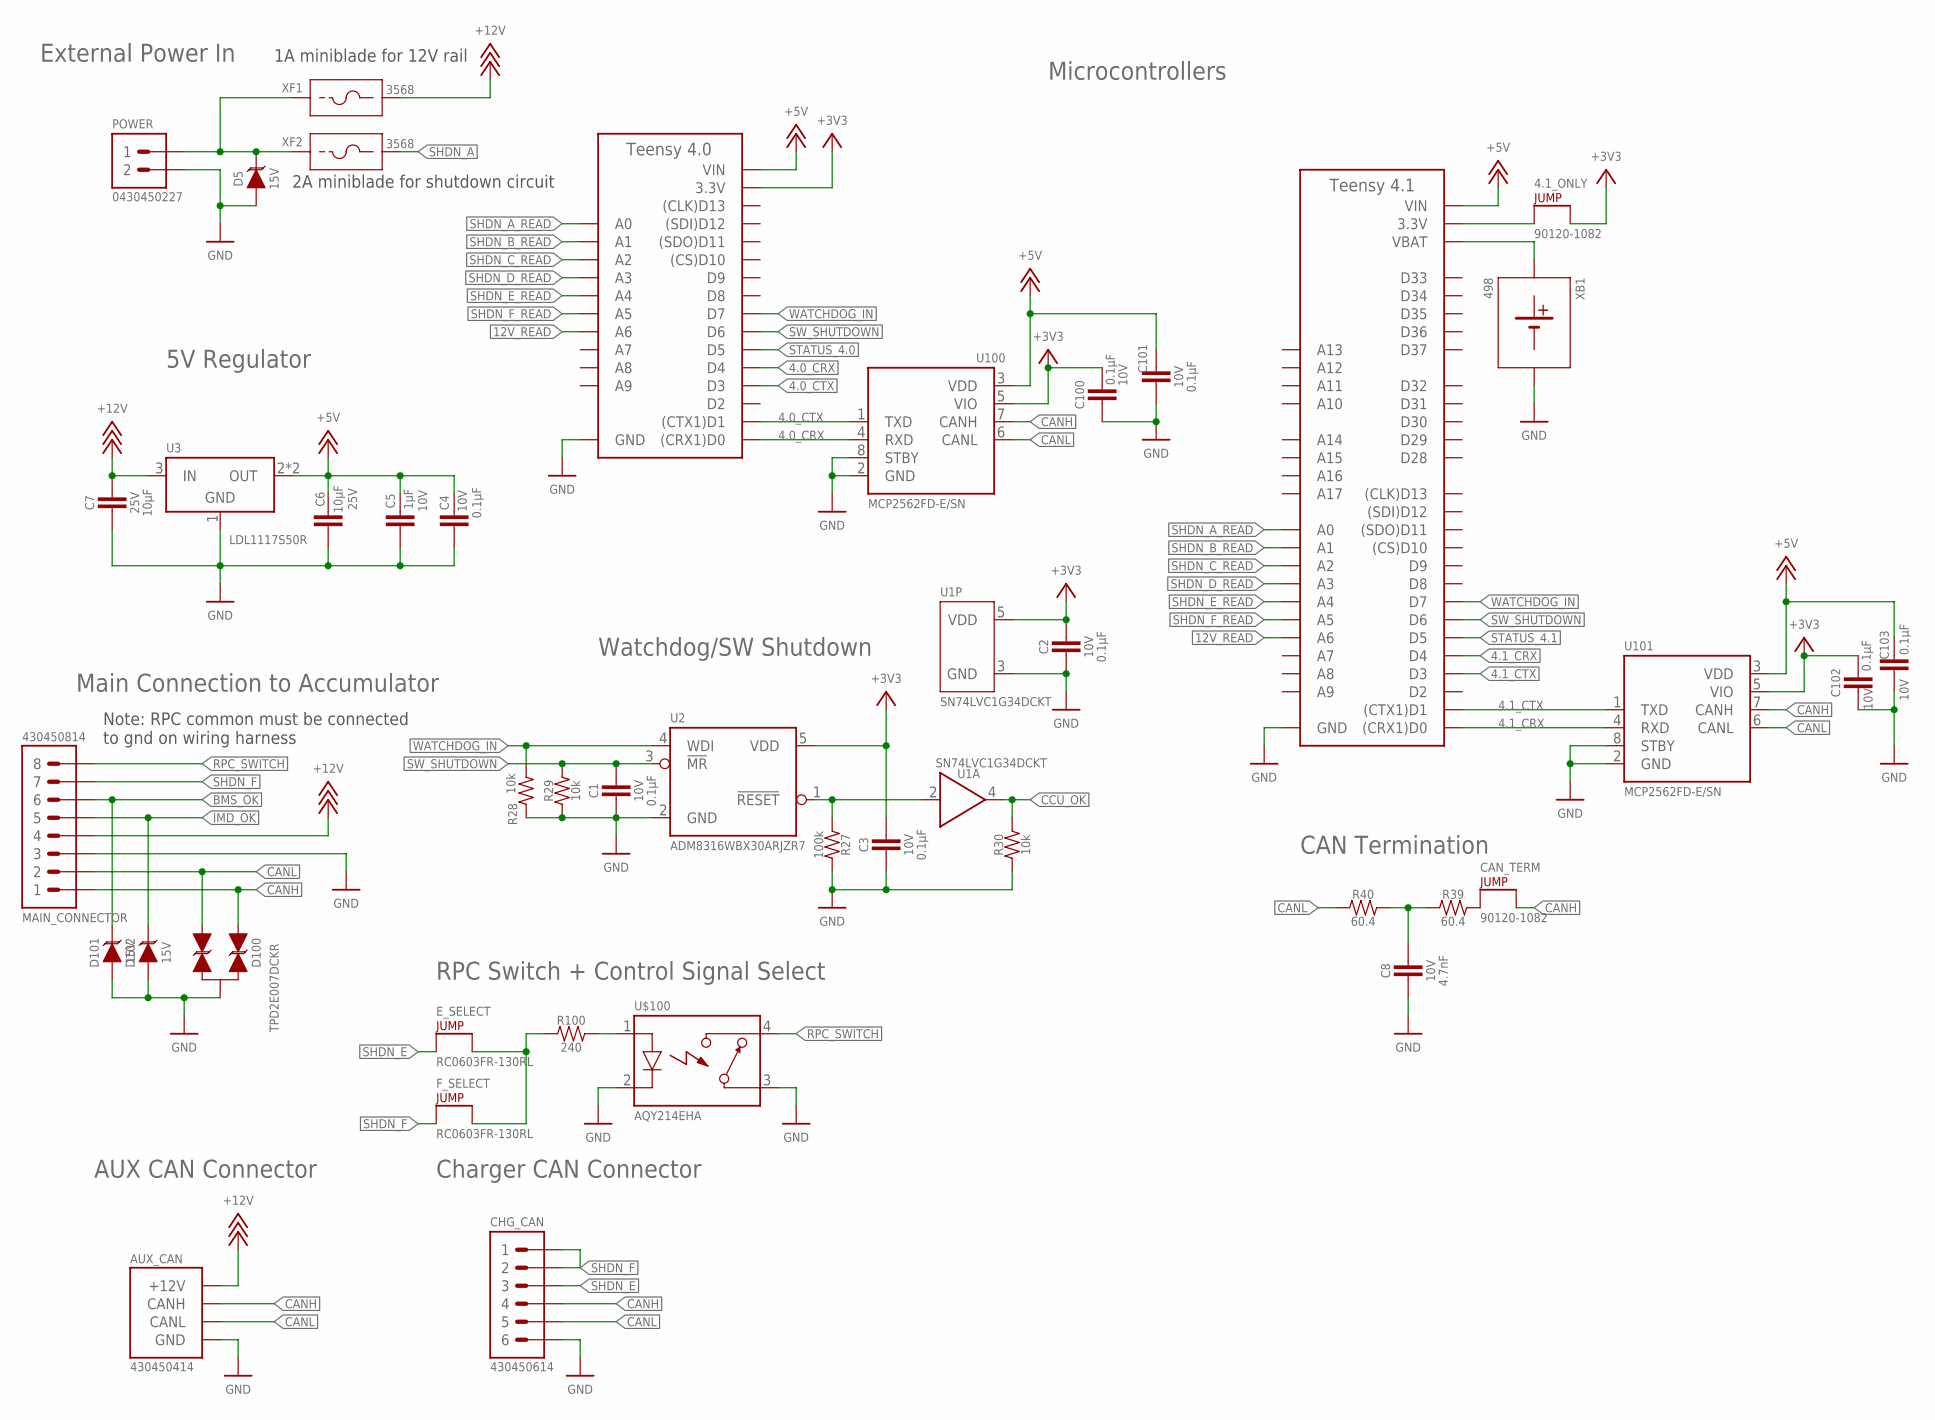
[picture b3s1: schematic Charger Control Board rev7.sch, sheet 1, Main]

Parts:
4.1_ONLY: JUMPER__1X02; 1X02
A1: TEENSY_4.1; TEENSY_LONG_EXT
A2: TEENSY_4.0; TEENSY_SHORT
AUX_CAN: CONNECTOR-CAN_MF_T_V_; MOLEX_MICROFIT_PTH_VERTICAL_04_DUAL
C1, C2, C3, C4, C100, C101, C102, C103: CAPACITOR_0603_10V_0.1UF; 0603-CAP
C5: CAPACITOR_0603_10V_1UF; 0603-CAP
C6, C7: CAPACITOR_0603_25V_10UF; 0603-CAP
C8: CAPACITOR_0603_10V_4.7NF; 0603-CAP
CAN_TERM: JUMPER__1X02; 1X02
CHG_CAN: CONNECTOR-6_MF_T_V_; MOLEX_MICROFIT_PTH_VERTICAL_06_DUAL
D5, D101, D102: TVS_15V; SOT-23
D100: TVS_BIDIRECTIONAL_DUAL; SC-70-3
E_SELECT: JUMPER_0603_; 0603-RES
F_SELECT: JUMPER_0603_; 0603-RES
MAIN_CONNECTOR: CONNECTOR-8_MF_T_V_; MOLEX_MICROFIT_PTH_VERTICAL_08_DUAL
POWER: CONNECTOR-2_μF_T_V_; MOLEX_MICROFIT_PTH_VERTICAL_02_DUAL
R27: RESISTOR_0603_100K; 0603-RES
R28, R29, R30: RESISTOR_0603_10K; 0603-RES
R39, R40: RESISTOR_0603_60.4; 0603-RES
R100: RESISTOR_0603_240; 0603-RES
U1: LOGICGATE_BUFFER; SC-70-5
U2: ADM8316WBX30; SOT-23-5
U3: VOLTAGE_REGULATOR_SOT-223_5V; SOT-223
U100, U101: MCP2562FD; SOIC-08(NARROW,0.15")
U$100: RELAY_SOLIDSTATE_NO; DIP-4
XB1: BATTERY_HOLDER_KEYSTONE_498; 498
XF1, XF2: FUSE_HOLDER_MINIBLADEPTH; 3568

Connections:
4.0_CRX: A2.D0 ((CRX1)D0), A2.D4, U100.4 (RXD)
4.0_CTX: A2.D1 ((CTX1)D1), A2.D3, U100.1 (TXD)
4.1_CRX: A1.D0 ((CRX1)D0), A1.D4, U101.4 (RXD)
4.1_CTX: A1.D1 ((CTX1)D1), A1.D3, U101.1 (TXD)
12V_READ: A1.D20 (A6), A2.D20 (A6); also elsewhere on the board
+3V3: 4.1_ONLY.2, A2.3.3V, C2.2, C3.2, C100.2, C102.2, U1.5 (VDD), U2.5 (VDD), U100.5 (VIO), U101.5 (VIO); also elsewhere on the board
+5V: A1.VIN, A2.VIN, C4.2, C5.1, C6.1, C101.2, C103.2, U3.2 (OUT), U3.4 (OUT), U100.3 (VDD), U101.3 (VDD); also elsewhere on the board
+12V: AUX_CAN.1 (+12V), C7.1, MAIN_CONNECTOR.4, U3.3 (IN), XF1.3 (2), XF1.4 (2); also elsewhere on the board
BMS_OK: D101.3 (C), MAIN_CONNECTOR.6; also elsewhere on the board
CANH: AUX_CAN.4 (CANH), CAN_TERM.2, CHG_CAN.4, D100.1 (C1), MAIN_CONNECTOR.1, U100.7 (CANH), U101.7 (CANH)
CANL: AUX_CAN.3 (CANL), CHG_CAN.5, D100.2 (C2), MAIN_CONNECTOR.2, R40.1, U100.6 (CANL), U101.6 (CANL)
CCU_OK: R30.2, U1.4 (OUT); also elsewhere on the board
GND: A1.AGND/GND (GND), A1.GND, A1.GND@2 (GND), A2.AGND/GND (GND), A2.GND, AUX_CAN.2 (GND), C1.1, C2.1, C3.1, C4.1, C5.2, C6.2, C7.2, C8.2, C100.1, C101.1, C102.1, C103.1, CHG_CAN.6, D5.1 (A), D100.3 (A), D101.1 (A), D102.1 (A), MAIN_CONNECTOR.3, POWER.2, R27.2, R28.2, R29.1, R30.1, U1.3 (GND), U2.2 (GND), U3.1 (GND), U100.2 (GND), U100.8 (STBY), U101.2 (GND), U101.8 (STBY), U$100.2 (CONTROL-), U$100.3 (CONTACT1), XB1.2 (MINUS); also elsewhere on the board
IMD_OK: D102.3 (C), MAIN_CONNECTOR.5; also elsewhere on the board
unnamed: D5.3 (C), POWER.1, XF1.1, XF1.2 (1), XF2.1, XF2.2 (1)
unnamed: R27.1, U1.2 (IN), U2.1 (!RESET!)
unnamed: CAN_TERM.1, R39.2
unnamed: E_SELECT.2, F_SELECT.2, R100.1
unnamed: A1.VBAT, XB1.1 (PLUS)
unnamed: C8.1, R39.1, R40.2
unnamed: R100.2, U$100.1 (CONTROL+)
unnamed: 4.1_ONLY.1, A1.3V3 (3.3V), A1.3V3@2 (3.3V), A1.3V3@3 (3.3V)
RPC_SWITCH: MAIN_CONNECTOR.8, U$100.4 (CONTACT2)
SHDN_A: XF2.3 (2), XF2.4 (2); also elsewhere on the board
SHDN_A_READ: A1.D14 (A0), A2.D14 (A0); also elsewhere on the board
SHDN_B_READ: A1.D15 (A1), A2.D15 (A1); also elsewhere on the board
SHDN_C_READ: A1.D16 (A2), A2.D16 (A2); also elsewhere on the board
SHDN_D_READ: A1.D17 (A3), A2.D17 (A3); also elsewhere on the board
SHDN_E: CHG_CAN.3, E_SELECT.1; also elsewhere on the board
SHDN_E_READ: A1.D18 (A4), A2.D18 (A4); also elsewhere on the board
SHDN_F: CHG_CAN.1, CHG_CAN.2, F_SELECT.1, MAIN_CONNECTOR.7; also elsewhere on the board
SHDN_F_READ: A1.D19 (A5), A2.D19 (A5); also elsewhere on the board
STATUS_4.0: A2.D5; also elsewhere on the board
STATUS_4.1: A1.D5; also elsewhere on the board
SW_SHUTDOWN: A1.D6, A2.D6, C1.2, R29.2, U2.3 (!MR!)
WATCHDOG_IN: A1.D7, A2.D7, R28.1, U2.4 (WDI)

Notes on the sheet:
External Power In
5V Regulator
Main Connection to Accumulator
CAN Termination
Microcontrollers
Watchdog/SW Shutdown
Charger CAN Connector
AUX CAN Connector
1A miniblade for 12V rail
2A miniblade for shutdown circuit
RPC Switch + Control Signal Select
Note: RPC common must be connected to gnd on wiring harness
